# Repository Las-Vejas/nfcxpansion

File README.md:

# nfcxpansion

This is an NFC module for the [Hackxpansion console](https://github.com/hackclub/hackxpansion).

It utilises the ST25DV04K-JFR6D3 NFC chip that can be written to and read from. My intention with this module is to let fellow hackers open it like a communication port for their apps.

|||
|----|-----|
|||

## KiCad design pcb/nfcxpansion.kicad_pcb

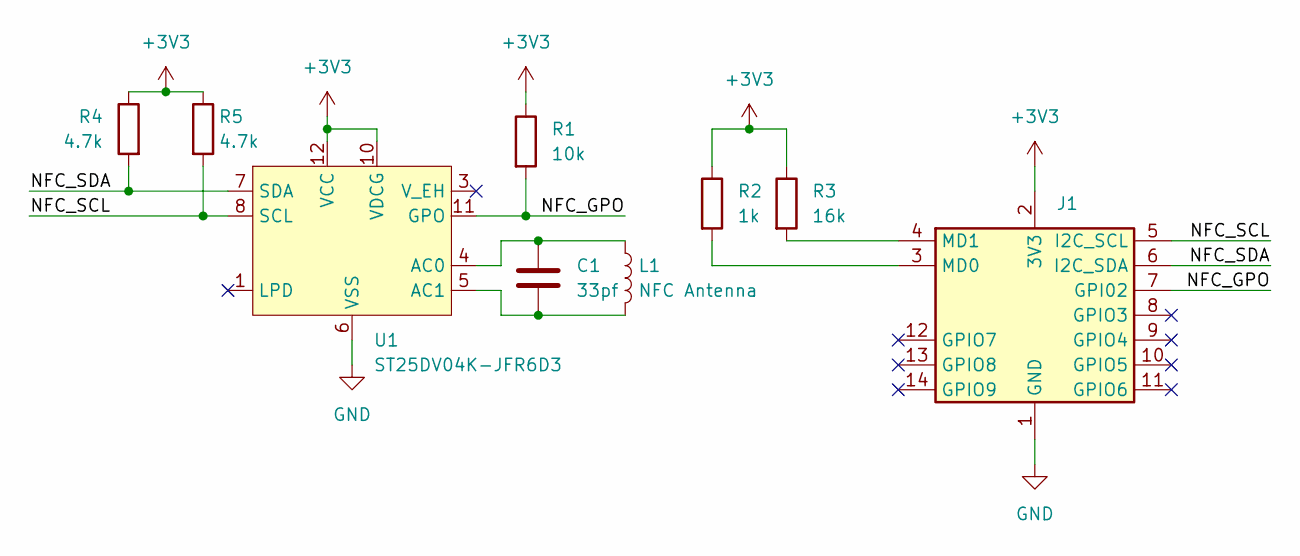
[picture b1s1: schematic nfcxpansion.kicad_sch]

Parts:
C1: 33pf; C_0402_1005Metric; LCSC Part # C5137486
J1: Male_Module
L1: NFC Antenna; 3ST25_NFC_2p03uH
R1: 10k; R_0402_1005Metric; LCSC Part # C2906861
R2: 1k; R_0402_1005Metric; LCSC Part # C140197
R3: 16k; R_0402_1005Metric; LCSC Part # C324823
R4, R5: 4.7k; R_0402_1005Metric; LCSC Part # C140158
U1: ST25DV04K-JFR6D3; ST_UFDFPN-12-1EP_3x3mm_P0.5mm_EP1.4x2.55mm; LCSC Part # C2654815

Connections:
+3V3: J1.2 (3V3), R1.1, R2.1, R3.1, R4.1, R5.1, U1.10 (VDCG), U1.12 (VCC)
/NFC_GPO: J1.7 (GPI02), R1.2, U1.11 (GPO)
/NFC_SCL: J1.5 (I2C_SCL), R5.2, U1.8 (SCL)
/NFC_SDA: J1.6 (I2C_SDA), R4.2, U1.7 (SDA)
GND: J1.1 (GND), U1.6 (VSS)
unnamed: J1.3 (MD0), R2.2
unnamed: J1.4 (MD1), R3.2
unnamed: C1.1, L1.1, U1.4 (AC0)
unnamed: C1.2, L1.2, U1.5 (AC1)

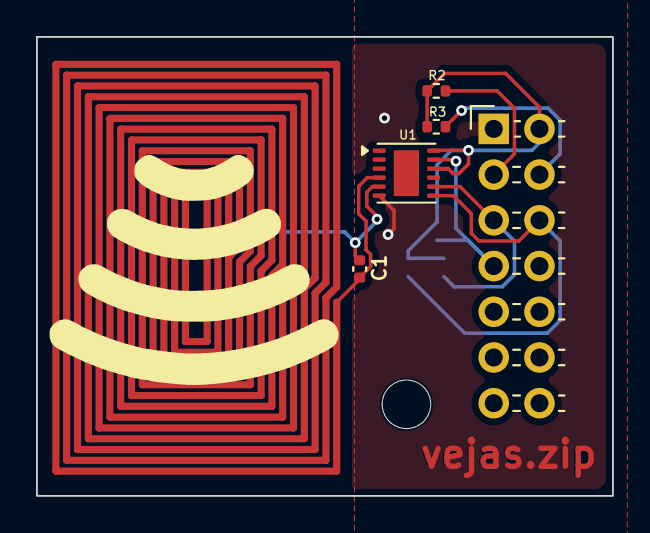
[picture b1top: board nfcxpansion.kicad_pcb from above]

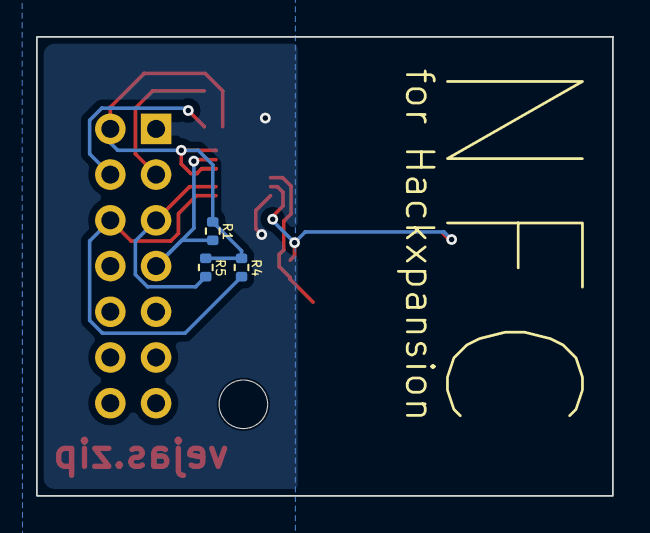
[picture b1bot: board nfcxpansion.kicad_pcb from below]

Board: 2 copper layers, 32.0 x 25.5 mm, 9 parts (3 on the bottom side), 9 nets.

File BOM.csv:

Reference,Price,Qty,Value,LCSC Part #
C1,0.3,1,33pf,C5137486
J1,0.24,1,N/A,N/A
R1,0.15,1,10k,C2906861
R2,0.14,1,1k,C140197
R3,0.14,1,16k,C324823
"R4,R5",0.14,2,4.7k,C140158
U1,0.91,1,ST25DV04K-JFR6D3,C2654815
PCB,4,5,N/A,N/A
Stencil,3.07,1,N/A,N/A
TOTAL,9.09,,N/A,N/A
